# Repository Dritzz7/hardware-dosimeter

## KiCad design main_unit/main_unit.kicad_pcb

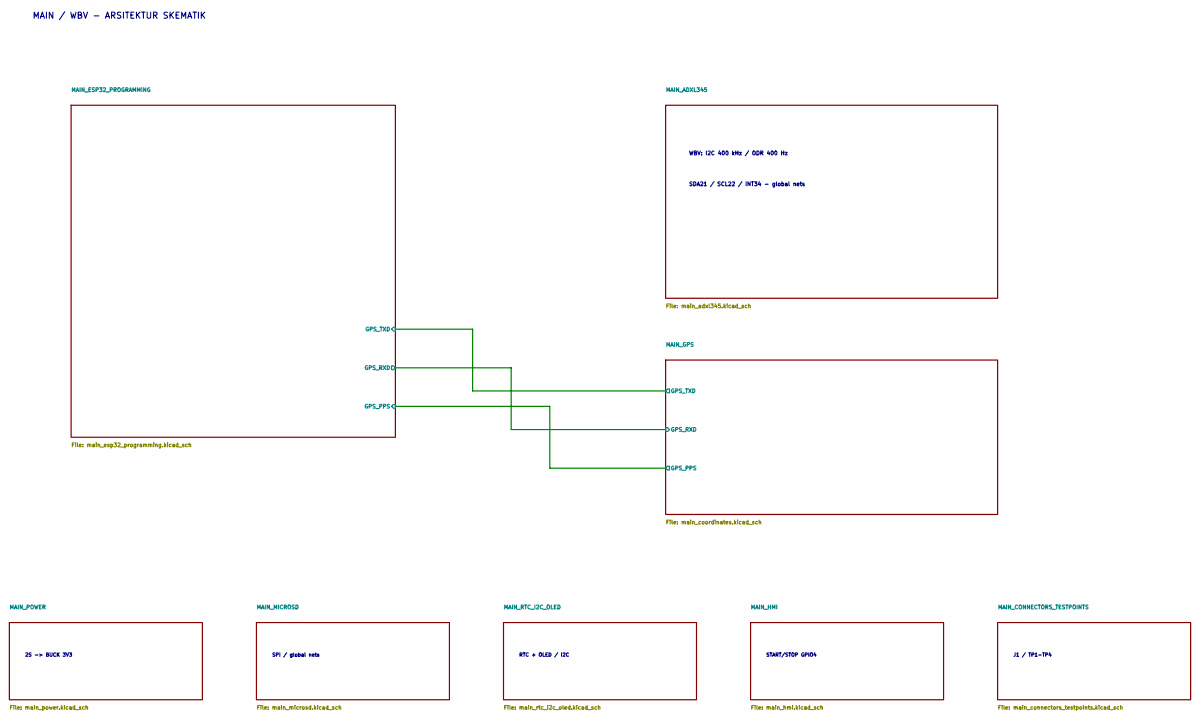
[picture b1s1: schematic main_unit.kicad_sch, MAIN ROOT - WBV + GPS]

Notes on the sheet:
2S -> BUCK 3V3
MAIN / WBV - ARSITEKTUR SKEMATIK
SPI / global nets
RTC + OLED / I2C
WBV: I2C 400 kHz / ODR 400 Hz
START/STOP GPIO4
SDA21 / SCL22 / INT34 - global nets
J1 / TP1-TP4

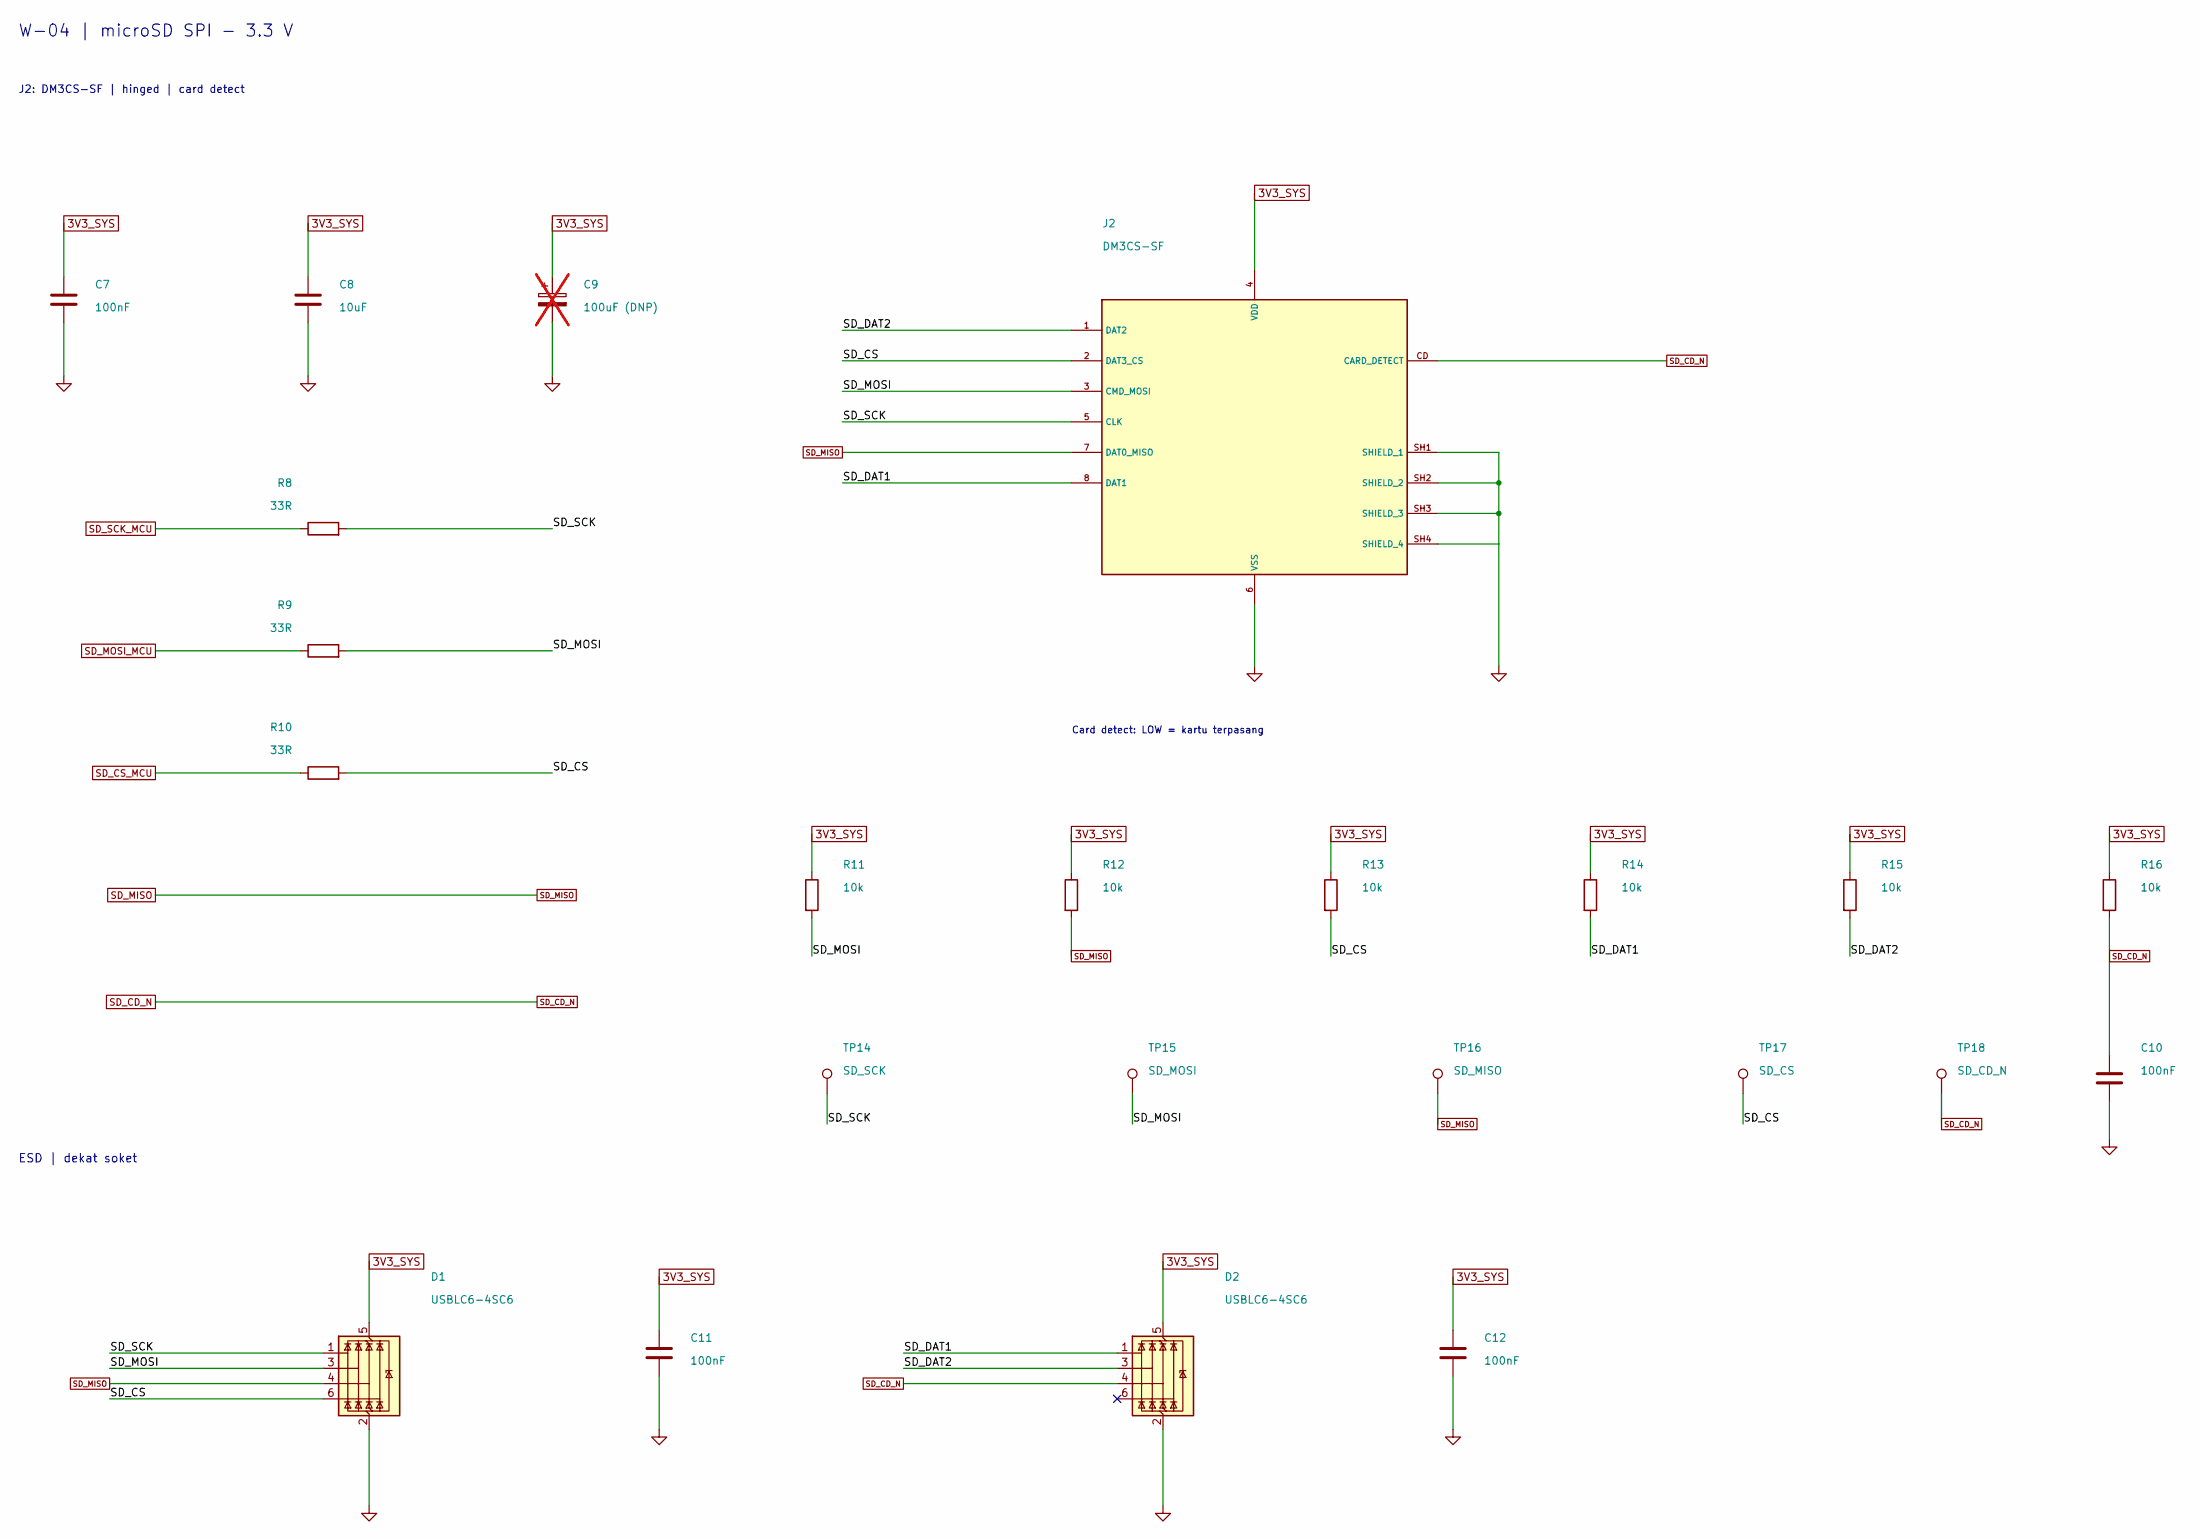
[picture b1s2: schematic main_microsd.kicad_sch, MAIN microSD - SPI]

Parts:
C7, C10, C11, C12: 100nF; C_0805_2012Metric; MPN C0805C104K5RACTU; LCSC Part # C3018562
C8: 10uF; C_0805_2012Metric; MPN CL21A106KAYNNNE; LCSC Part # C15850
C9: 100uF (DNP); CP_Radial_D5.0mm_P2.00mm_H11mm_Panasonic_FR; MPN EEUFR1C101; not fitted
D1, D2: USBLC6-4SC6; SOT-23-6_USBLC6-4SC6_ST; MPN USBLC6-4SC6; LCSC Part # C111212
J2: DM3CS-SF; microSD_Hirose_DM3CS-SF; MPN DM3CS-SF; LCSC Part # C202111
R8, R9, R10: 33R; R_0805_2012Metric; MPN RC0805FR-0733RL; LCSC Part # C126353
R11, R12, R13, R14, R15, R16: 10k; R_0805_2012Metric; MPN RC0805FR-0710KL; LCSC Part # C84376
TP14: SD_SCK; TestPoint_Pad_D1.5mm; MPN N/A - PCB copper feature
TP15: SD_MOSI; TestPoint_Pad_D1.5mm; MPN N/A - PCB copper feature
TP16: SD_MISO; TestPoint_Pad_D1.5mm; MPN N/A - PCB copper feature
TP17: SD_CS; TestPoint_Pad_D1.5mm; MPN N/A - PCB copper feature
TP18: SD_CD_N; TestPoint_Pad_D1.5mm; MPN N/A - PCB copper feature

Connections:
3V3_SYS: C7.1, C8.1, C9.1, C11.1, C12.1, D1.5 (VBUS), D2.5 (VBUS), J2.4 (VDD), R11.1, R12.1, R13.1, R14.1, R15.1, R16.1; also elsewhere on the board
/MAIN_MICROSD/SD_CS: D1.6 (I/O4), J2.2 (DAT3_CS), R10.2, R13.2, TP17.1 (1_1)
/MAIN_MICROSD/SD_DAT1: D2.1 (I/O1), J2.8 (DAT1), R14.2
/MAIN_MICROSD/SD_DAT2: D2.3 (I/O2), J2.1 (DAT2), R15.2
/MAIN_MICROSD/SD_MOSI: D1.3 (I/O2), J2.3 (CMD_MOSI), R9.2, R11.2, TP15.1 (1_1)
/MAIN_MICROSD/SD_SCK: D1.1 (I/O1), J2.5 (CLK), R8.2, TP14.1 (1_1)
GND: C7.2, C8.2, C9.2, C10.2, C11.2, C12.2, D1.2 (GND), D2.2 (GND), J2.6 (VSS), J2.SH1 (SHIELD_1), J2.SH2 (SHIELD_2), J2.SH3 (SHIELD_3), J2.SH4 (SHIELD_4); also elsewhere on the board
SD_CD_N: C10.1, D2.4 (I/O3), J2.CD (CARD_DETECT), R16.2, TP18.1 (1_1); also elsewhere on the board
SD_CS_MCU: R10.1; also elsewhere on the board
SD_MISO: D1.4 (I/O3), J2.7 (DAT0_MISO), R12.2, TP16.1 (1_1); also elsewhere on the board
SD_MOSI_MCU: R9.1; also elsewhere on the board
SD_SCK_MCU: R8.1; also elsewhere on the board

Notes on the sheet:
Card detect: LOW = kartu terpasang
ESD | dekat soket
W-04 | microSD SPI - 3.3 V
J2: DM3CS-SF | hinged | card detect

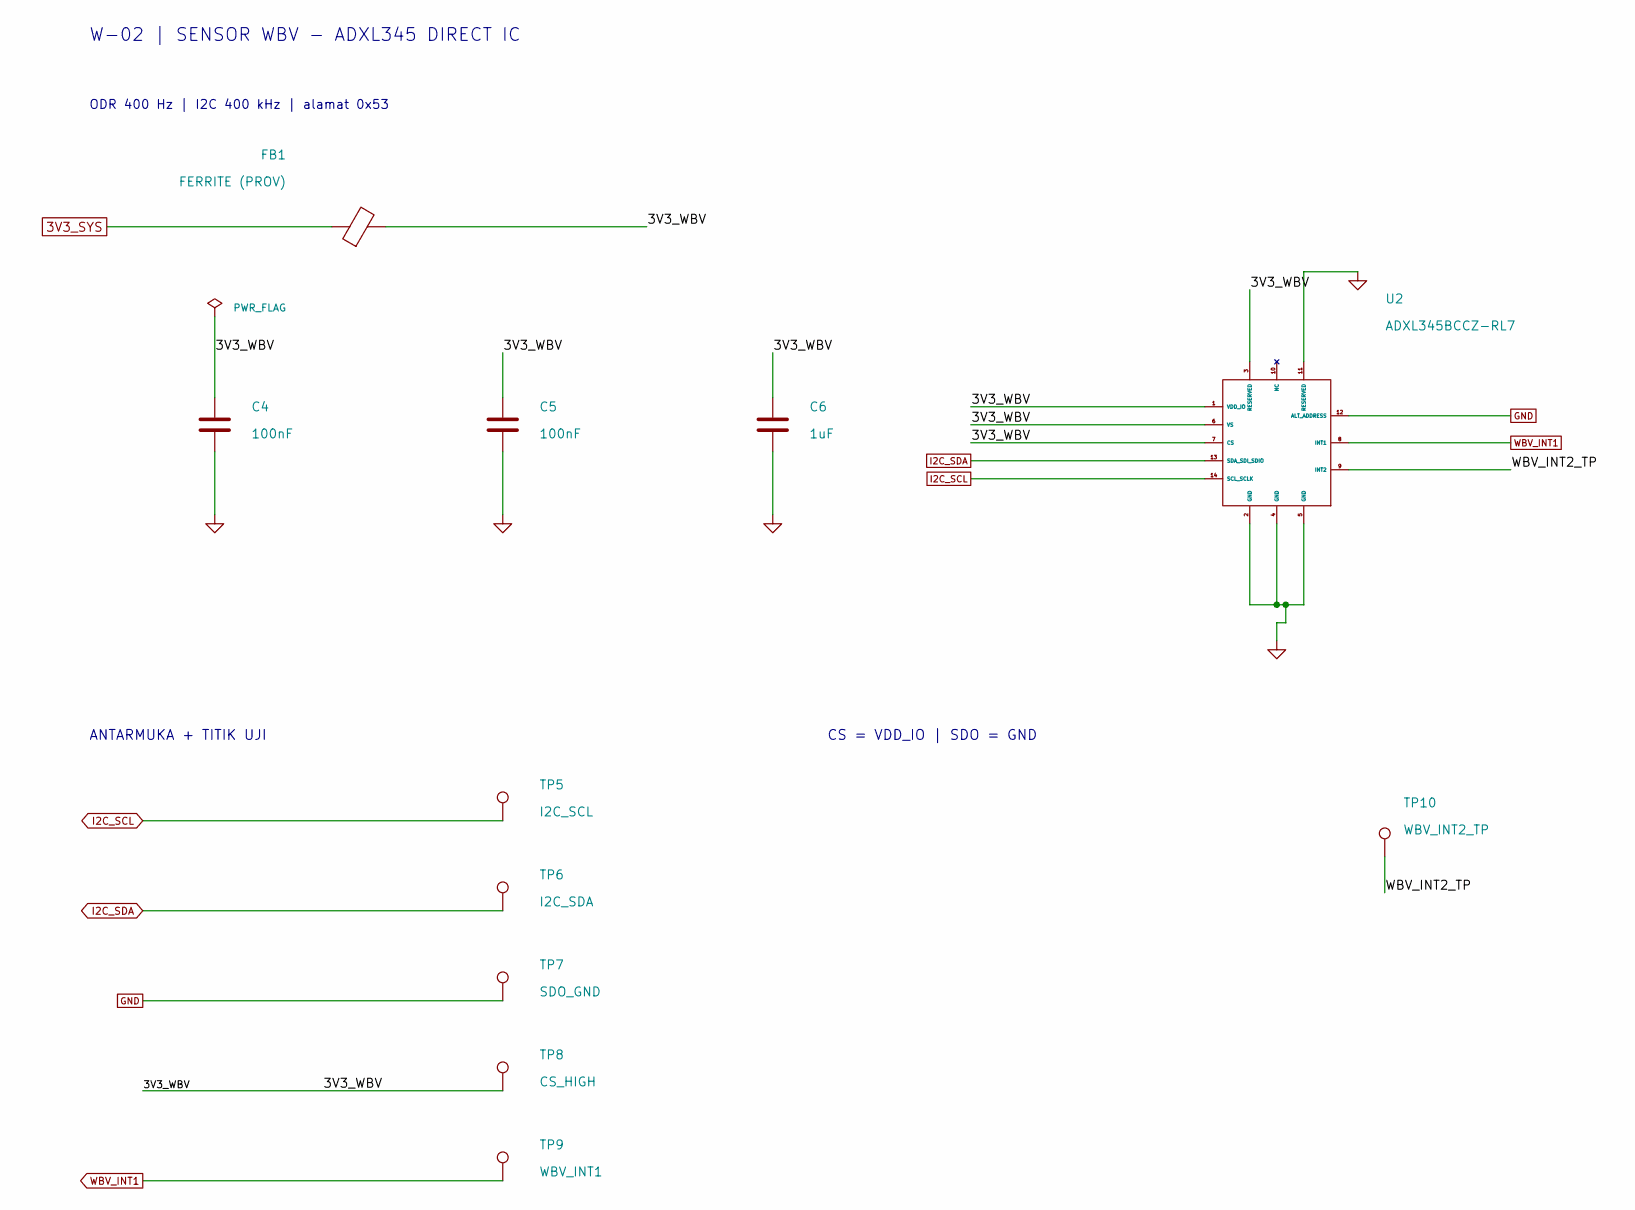
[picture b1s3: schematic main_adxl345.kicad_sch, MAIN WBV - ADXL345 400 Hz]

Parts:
C4, C5: 100nF; C_0805_2012Metric; MPN C0805C104K5RACTU; LCSC Part # C3018562
C6: 1uF; C_0805_2012Metric; MPN C0805C105K4RACTU; LCSC Part # C2167376
FB1: FERRITE (PROV); L_0805_2012Metric; MPN BLM21PG601SN1D; LCSC Part # C41556732
TP5: I2C_SCL; TestPoint_Pad_D1.5mm; MPN N/A - PCB copper feature
TP6: I2C_SDA; TestPoint_Pad_D1.5mm; MPN N/A - PCB copper feature
TP7: SDO_GND; TestPoint_Pad_D1.5mm; MPN N/A - PCB copper feature
TP8: CS_HIGH; TestPoint_Pad_D1.5mm; MPN N/A - PCB copper feature
TP9: WBV_INT1; TestPoint_Pad_D1.5mm; MPN N/A - PCB copper feature
TP10: WBV_INT2_TP; TestPoint_Pad_D1.5mm; MPN N/A - PCB copper feature
U2: ADXL345BCCZ-RL7; ADXL345_CC-14-1_ADI_JLC; MPN ADXL345BCCZ-RL7; LCSC Part # C9667

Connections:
3V3_SYS: FB1.1; also elsewhere on the board
/MAIN_ADXL345/3V3_WBV: C4.1, C5.1, C6.1, FB1.2, TP8.1 (1_1), U2.1 (VDD_IO), U2.3 (RESERVED), U2.6 (VS), U2.7 (CS)
/MAIN_ADXL345/WBV_INT2_TP: TP10.1 (1_1), U2.9 (INT2)
GND: C4.2, C5.2, C6.2, TP7.1 (1_1), U2.2 (GND), U2.4 (GND), U2.5 (GND), U2.11 (RESERVED), U2.12 (ALT_ADDRESS); also elsewhere on the board
I2C_SCL: TP5.1 (1_1), U2.14 (SCL_SCLK); also elsewhere on the board
I2C_SDA: TP6.1 (1_1), U2.13 (SDA_SDI_SDIO); also elsewhere on the board
WBV_INT1: TP9.1 (1_1), U2.8 (INT1); also elsewhere on the board

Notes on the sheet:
W-02 | SENSOR WBV - ADXL345 DIRECT IC
ODR 400 Hz | I2C 400 kHz | alamat 0x53
ANTARMUKA + TITIK UJI
CS = VDD_IO | SDO = GND

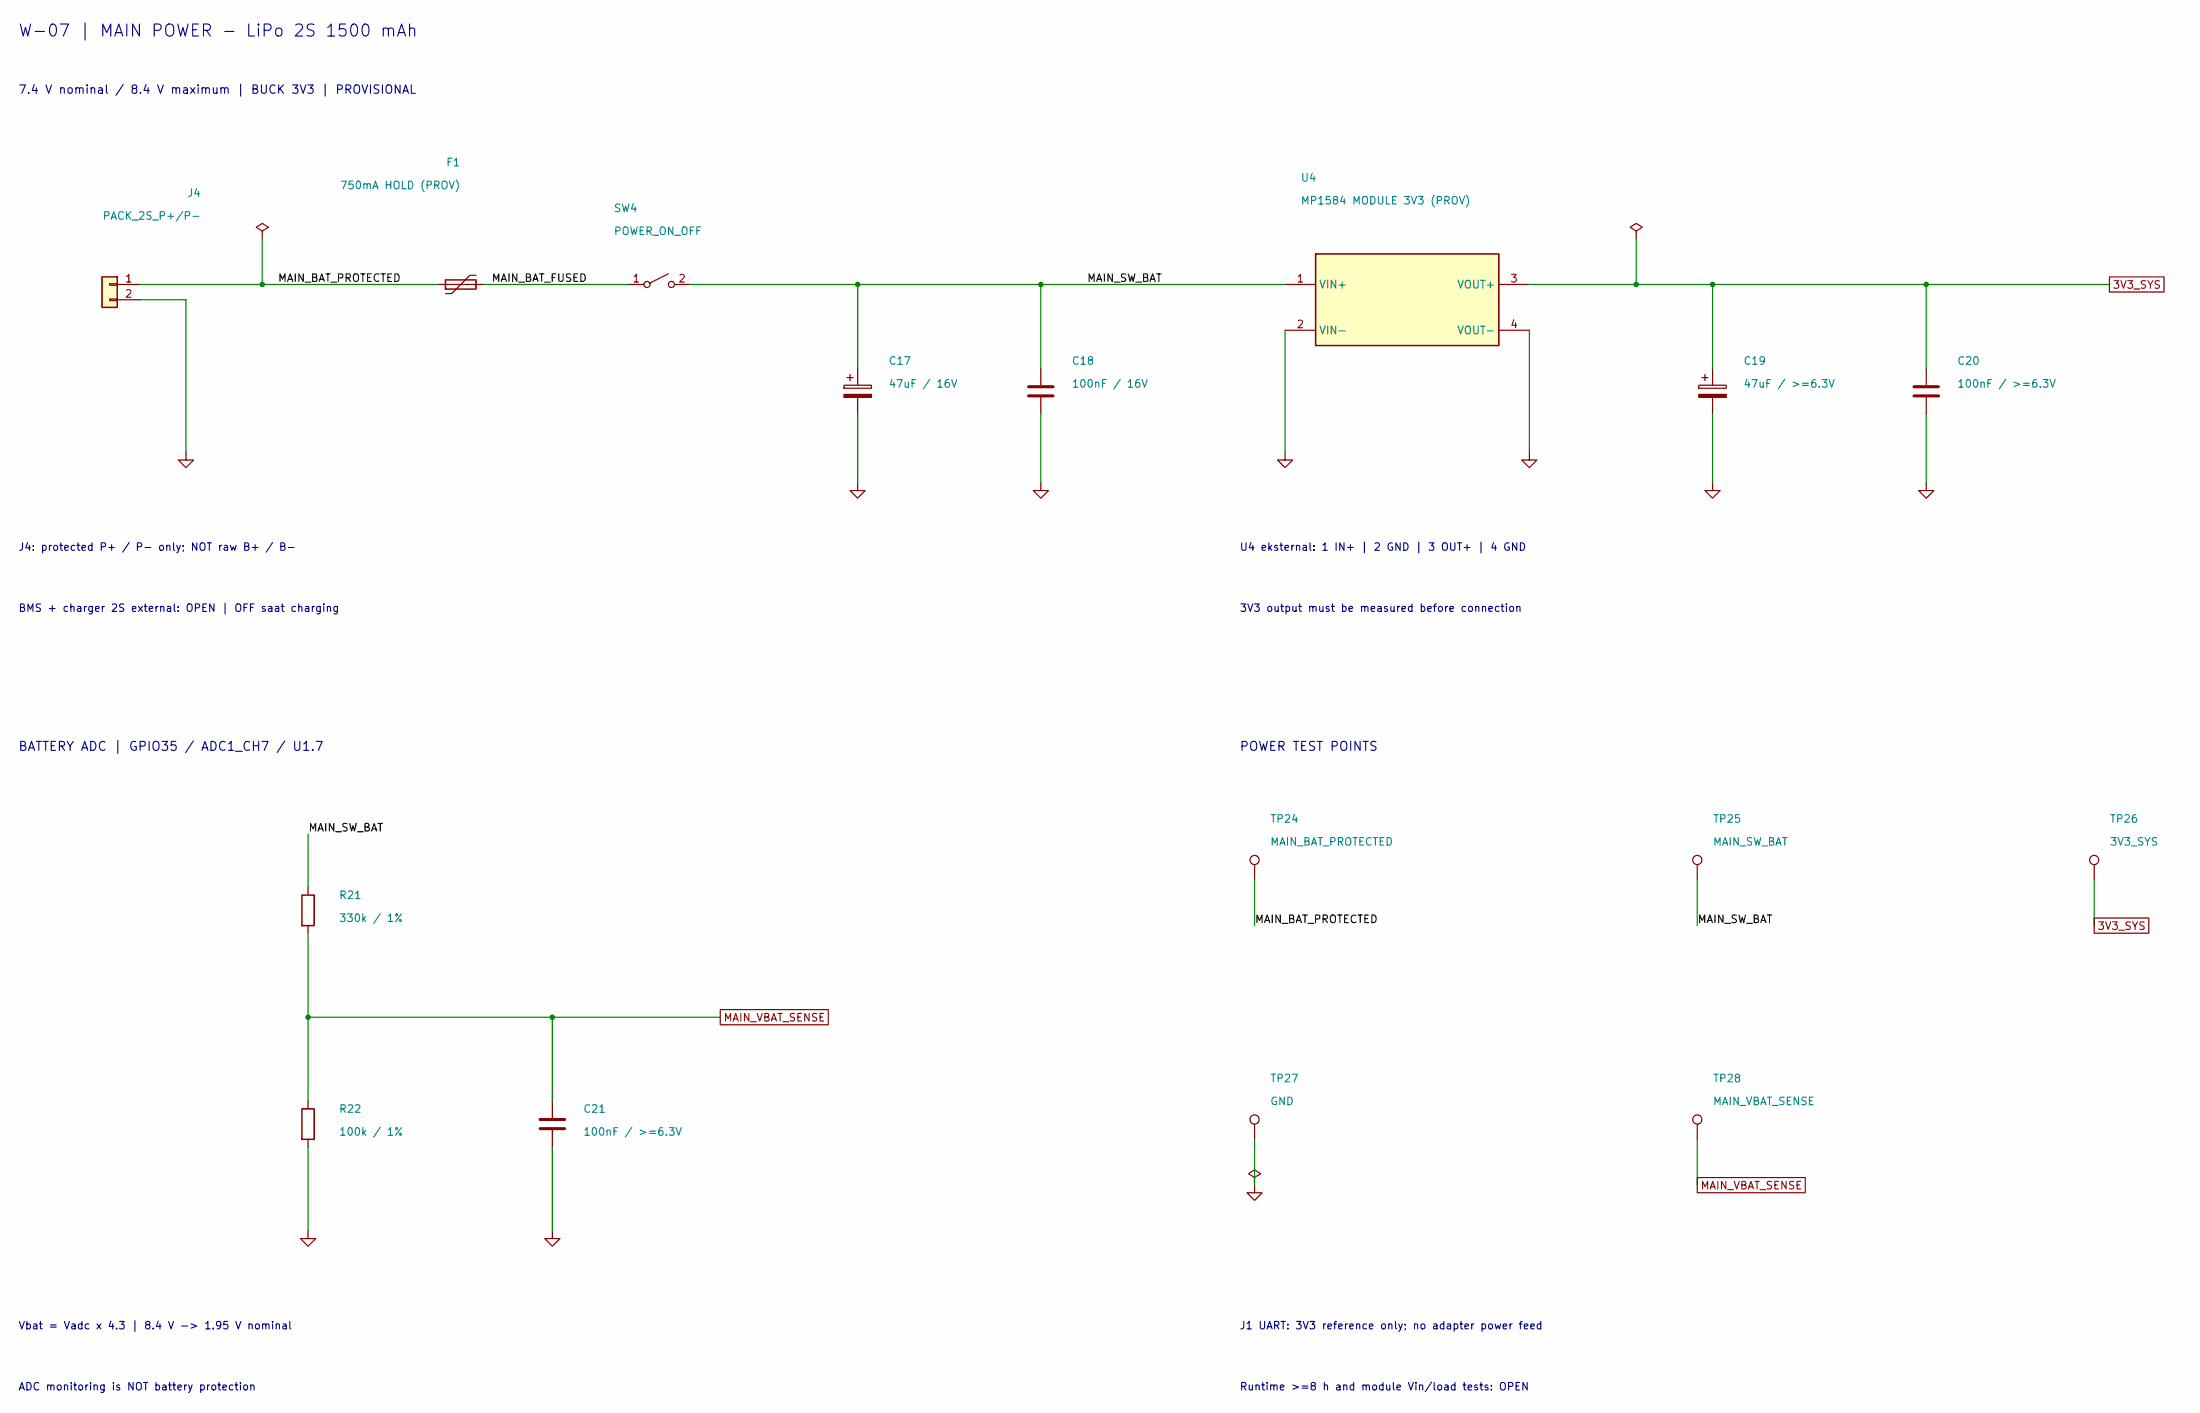
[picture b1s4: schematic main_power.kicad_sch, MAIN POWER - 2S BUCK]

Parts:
C17: 47uF / 16V; CP_Radial_D5.0mm_P2.00mm_H11mm_Panasonic_FR; MPN EEUFR1E470; LCSC Part # C407893
C18: 100nF / 16V; C_0805_2012Metric; MPN C0805C104K5RACTU; LCSC Part # C3018562
C19: 47uF / >=6.3V; CP_Radial_D5.0mm_P2.00mm_H11mm_Panasonic_FR; MPN EEUFR1E470; LCSC Part # C407893
C20, C21: 100nF / >=6.3V; C_0805_2012Metric; MPN C0805C104K5RACTU; LCSC Part # C3018562
F1: 750mA HOLD (PROV); Fuse_Bourns_MF-MSMF075_1812_Style1; MPN MF-MSMF075-2; LCSC Part # C84140
J4: PACK_2S_P+/P-; JST_XH_B2B-XH-A_1x02_P2.50mm_Vertical; MPN B2B-XH-A(LF)(SN); LCSC Part # C158012
R21: 330k / 1%; R_0805_2012Metric; MPN RC0805FR-07330KL; LCSC Part # C114528
R22: 100k / 1%; R_0805_2012Metric; MPN RC0805FR-07100KL; LCSC Part # C96346
SW4: POWER_ON_OFF; SolderWire-0.25sqmm_1x02_P4.2mm_D0.65mm_OD1.7mm; MPN OPEN - verify purchased part
TP24: MAIN_BAT_PROTECTED; TestPoint_Pad_D1.5mm; MPN N/A - PCB copper feature
TP25: MAIN_SW_BAT; TestPoint_Pad_D1.5mm; MPN N/A - PCB copper feature
TP26: 3V3_SYS; TestPoint_Pad_D1.5mm; MPN N/A - PCB copper feature
TP27: GND; TestPoint_Pad_D1.5mm; MPN N/A - PCB copper feature
TP28: MAIN_VBAT_SENSE; TestPoint_Pad_D1.5mm; MPN N/A - PCB copper feature
U4: MP1584 MODULE 3V3 (PROV); SolderWire-0.25sqmm_1x04_P4.2mm_D0.65mm_OD1.7mm; MPN OPEN - verify purchased part

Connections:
3V3_SYS: C19.1, C20.1, TP26.1 (1_1), U4.3 (VOUT+); also elsewhere on the board
/MAIN_POWER/MAIN_BAT_FUSED: F1.2, SW4.1 (A)
/MAIN_POWER/MAIN_BAT_PROTECTED: F1.1, J4.1, TP24.1 (1_1)
/MAIN_POWER/MAIN_SW_BAT: C17.1, C18.1, R21.1, SW4.2 (B), TP25.1 (1_1), U4.1 (VIN+)
GND: C17.2, C18.2, C19.2, C20.2, C21.2, J4.2, R22.2, TP27.1 (1_1), U4.2 (VIN-), U4.4 (VOUT-); also elsewhere on the board
MAIN_VBAT_SENSE: C21.1, R21.2, R22.1, TP28.1 (1_1); also elsewhere on the board

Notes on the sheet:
ADC monitoring is NOT battery protection
POWER TEST POINTS
Vbat = Vadc x 4.3 | 8.4 V -> 1.95 V nominal
Runtime >=8 h and module Vin/load tests: OPEN
J1 UART: 3V3 reference only; no adapter power feed
3V3 output must be measured before connection
U4 eksternal: 1 IN+ | 2 GND | 3 OUT+ | 4 GND
J4: protected P+ / P- only; NOT raw B+ / B-
7.4 V nominal / 8.4 V maximum | BUCK 3V3 | PROVISIONAL
BMS + charger 2S external: OPEN | OFF saat charging
W-07 | MAIN POWER - LiPo 2S 1500 mAh
BATTERY ADC | GPIO35 / ADC1_CH7 / U1.7

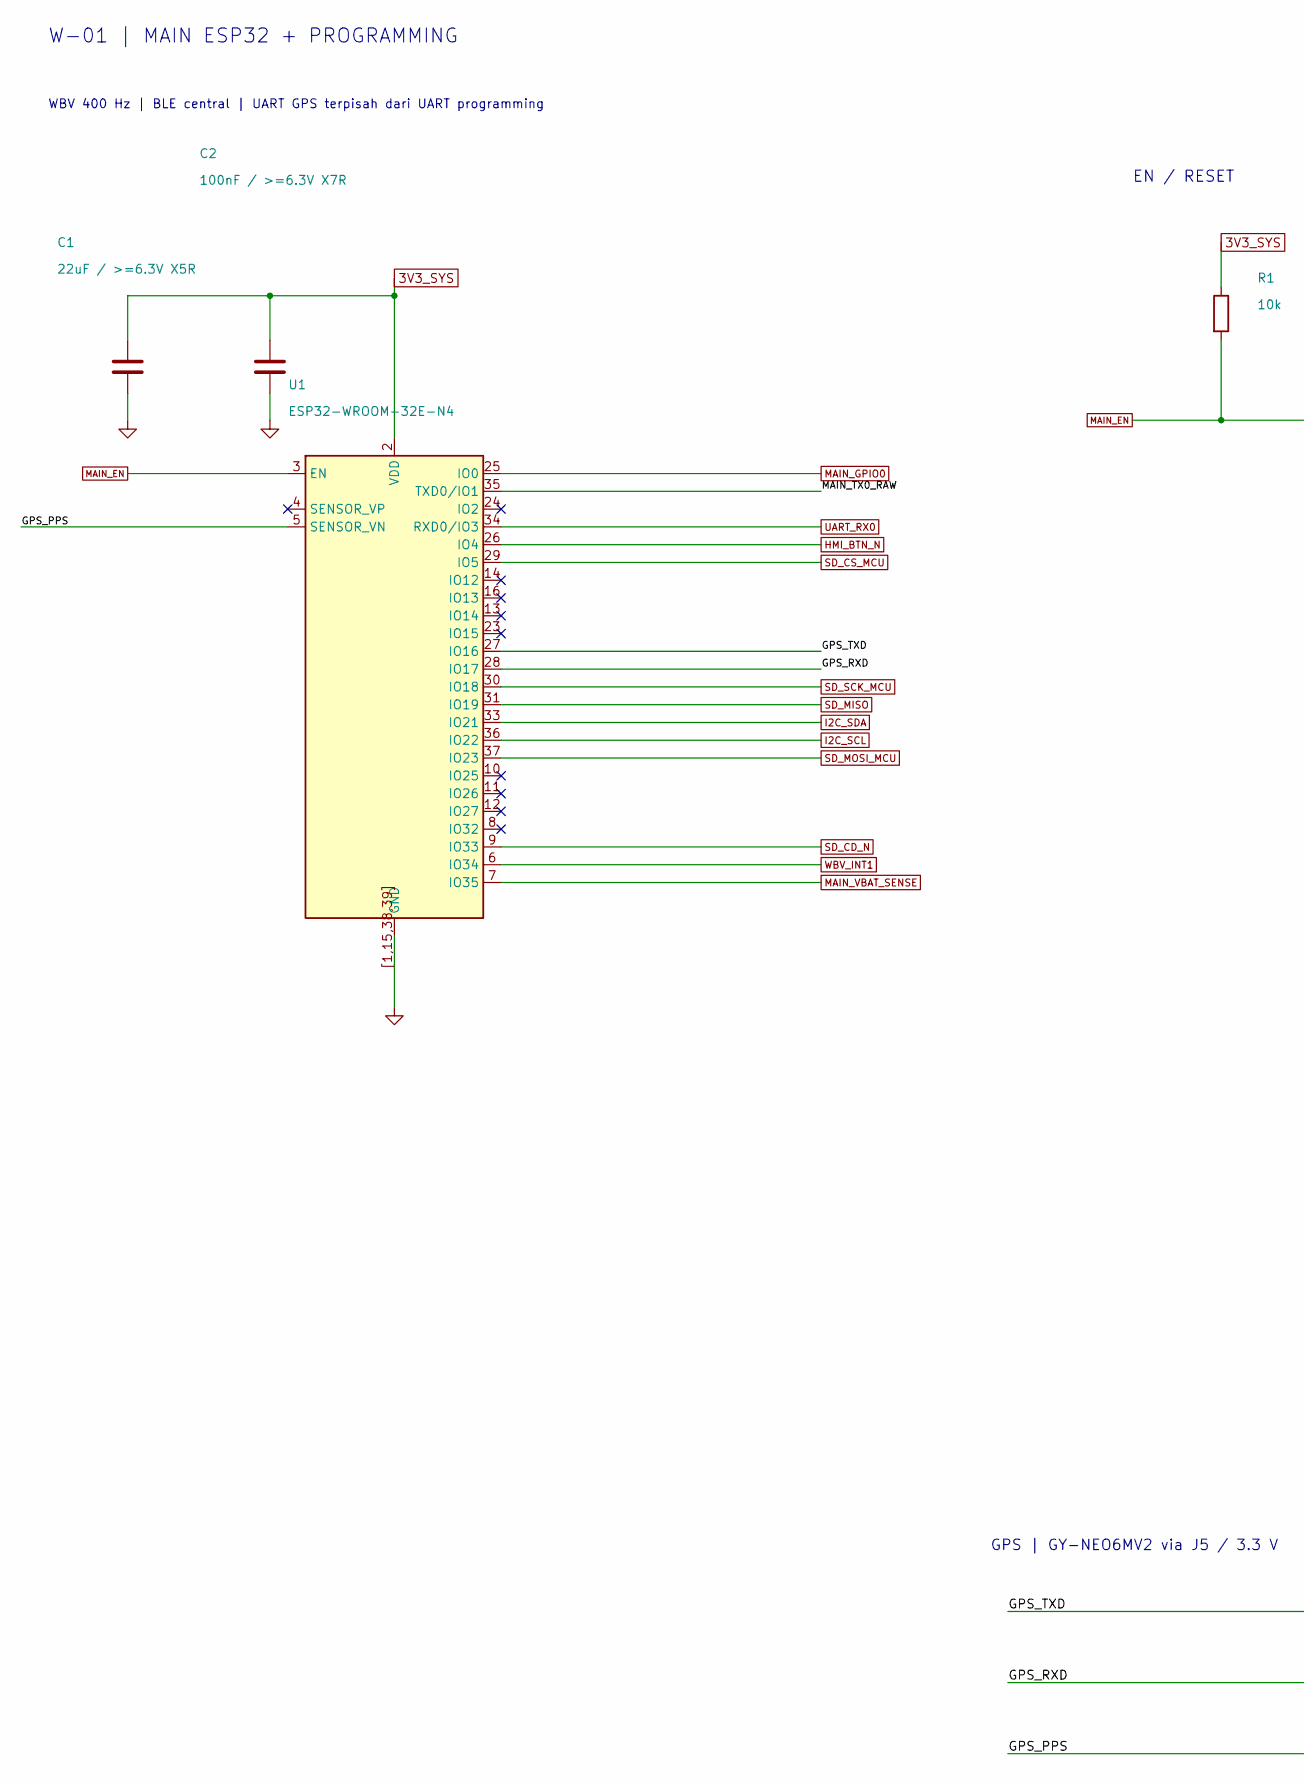
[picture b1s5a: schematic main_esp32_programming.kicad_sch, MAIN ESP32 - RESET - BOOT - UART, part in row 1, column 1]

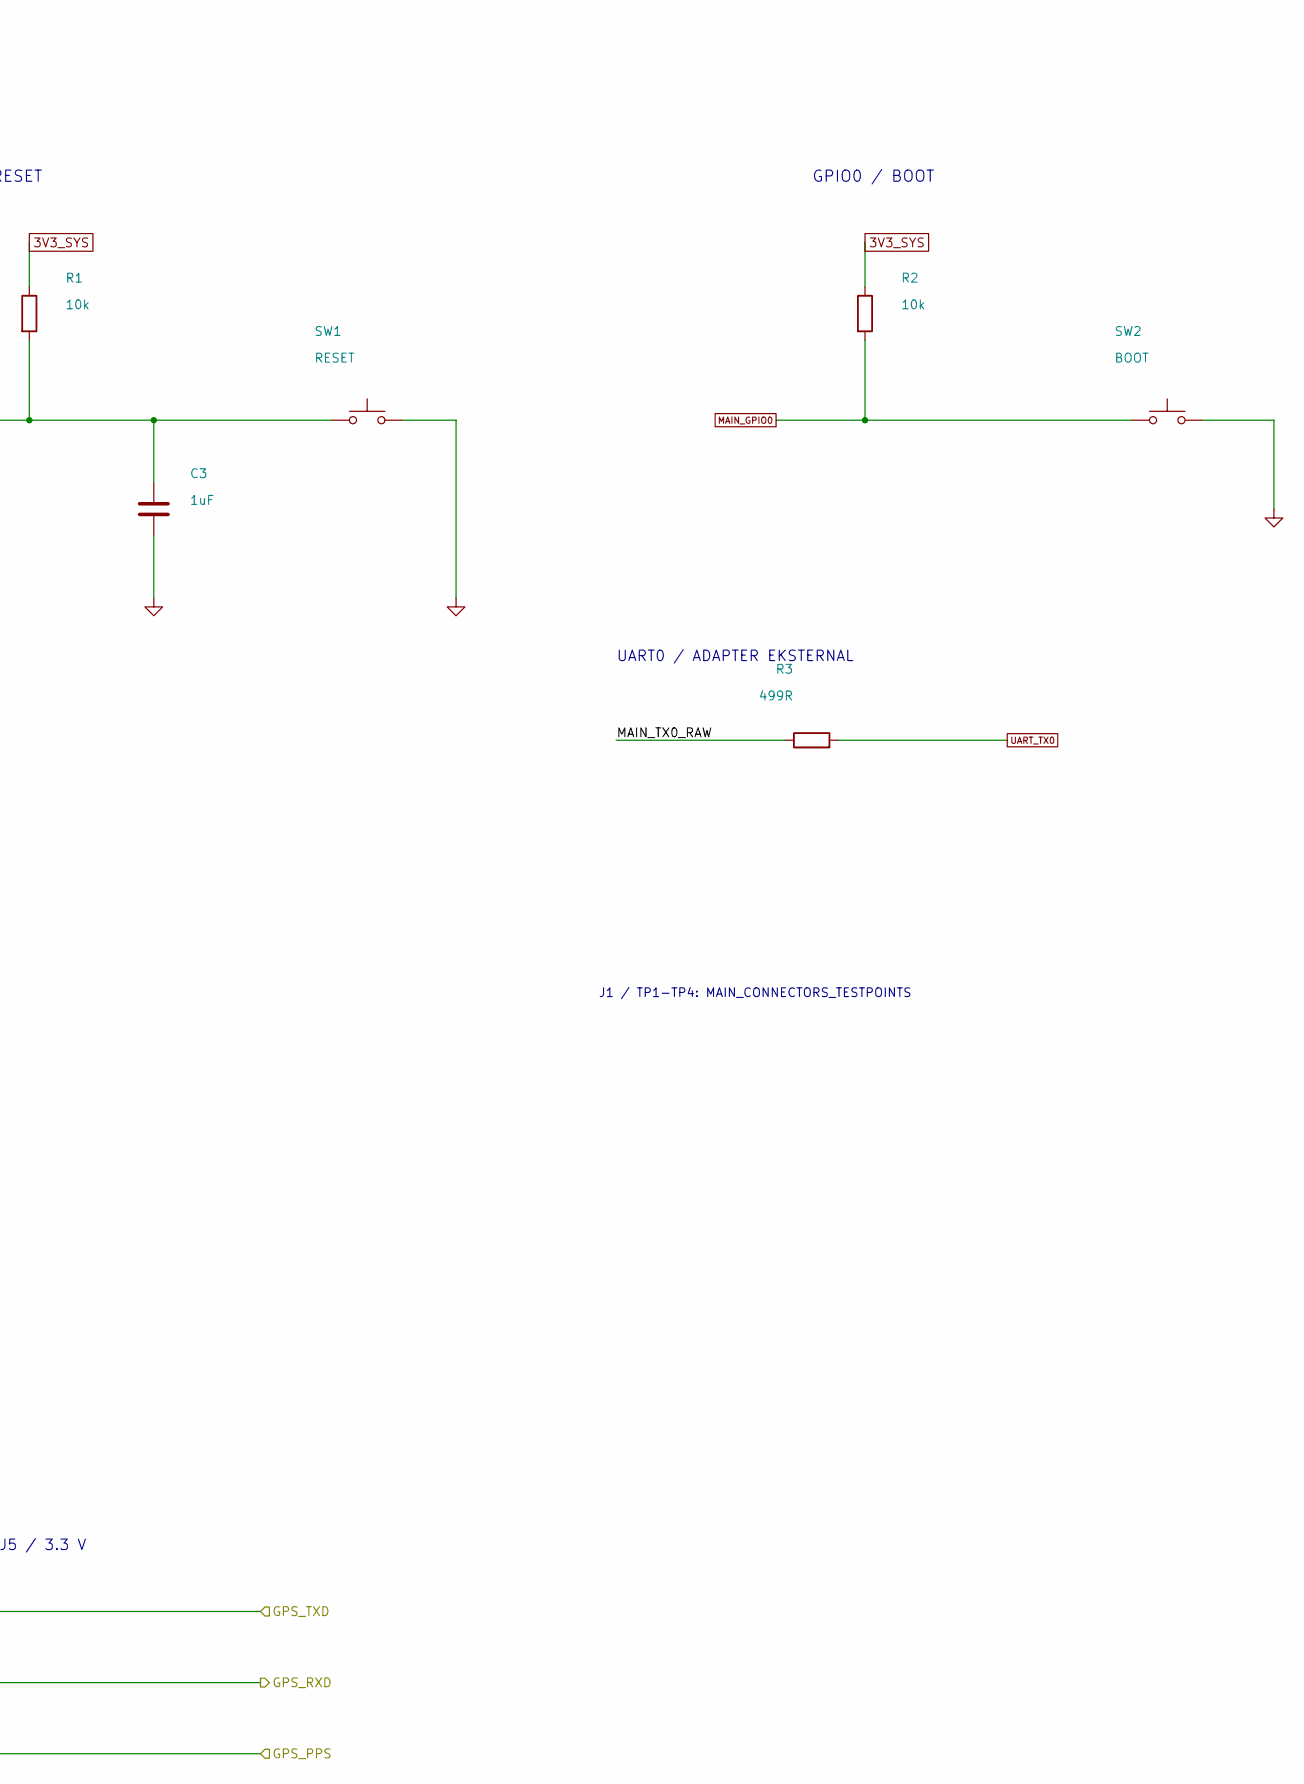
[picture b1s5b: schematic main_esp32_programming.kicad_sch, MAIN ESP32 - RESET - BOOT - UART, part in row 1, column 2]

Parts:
C1: 22uF / >=6.3V X5R; C_1206_3216Metric; MPN CL31A226KOHNNNE; LCSC Part # C90146
C2: 100nF / >=6.3V X7R; C_0805_2012Metric; MPN C0805C104K5RACTU; LCSC Part # C3018562
C3: 1uF; C_0805_2012Metric; MPN C0805C105K4RACTU; LCSC Part # C2167376
R1, R2: 10k; R_0805_2012Metric; MPN RC0805FR-0710KL; LCSC Part # C84376
R3: 499R; R_0805_2012Metric; MPN RC0805FR-07499RL; LCSC Part # C130458
SW1: RESET; SW_PUSH_6mm_H4.3mm; MPN B3F-1000; LCSC Part # C93157
SW2: BOOT; SW_PUSH_6mm_H4.3mm; MPN B3F-1000; LCSC Part # C93157
U1: ESP32-WROOM-32E-N4; ESP32-WROOM-32E_JLC_NoVia; MPN ESP32-WROOM-32E-N4; LCSC Part # C701341

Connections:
3V3_SYS: C1.1, C2.1, R1.1, R2.1, U1.2 (VDD); also elsewhere on the board
/MAIN_ESP32_PROGRAMMING/GPS_PPS: U1.5 (SENSOR_VN); also elsewhere on the board
/MAIN_ESP32_PROGRAMMING/GPS_RXD: U1.28 (IO17); also elsewhere on the board
/MAIN_ESP32_PROGRAMMING/GPS_TXD: U1.27 (IO16); also elsewhere on the board
/MAIN_ESP32_PROGRAMMING/MAIN_TX0_RAW: R3.1, U1.35 (TXD0/IO1)
GND: C1.2, C2.2, C3.2, SW1.2, SW2.2, U1.1 (GND), U1.15 (GND), U1.38 (GND), U1.39 (GND), U1.[1,15,38,39] (GND); also elsewhere on the board
HMI_BTN_N: U1.26 (IO4); also elsewhere on the board
I2C_SCL: U1.36 (IO22); also elsewhere on the board
I2C_SDA: U1.33 (IO21); also elsewhere on the board
MAIN_EN: C3.1, R1.2, SW1.1, U1.3 (EN); also elsewhere on the board
MAIN_GPIO0: R2.2, SW2.1, U1.25 (IO0); also elsewhere on the board
MAIN_VBAT_SENSE: U1.7 (IO35); also elsewhere on the board
SD_CD_N: U1.9 (IO33); also elsewhere on the board
SD_CS_MCU: U1.29 (IO5); also elsewhere on the board
SD_MISO: U1.31 (IO19); also elsewhere on the board
SD_MOSI_MCU: U1.37 (IO23); also elsewhere on the board
SD_SCK_MCU: U1.30 (IO18); also elsewhere on the board
UART_RX0: U1.34 (RXD0/IO3); also elsewhere on the board
UART_TX0: R3.2; also elsewhere on the board
WBV_INT1: U1.6 (IO34); also elsewhere on the board

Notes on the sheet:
W-01 | MAIN ESP32 + PROGRAMMING
GPS | GY-NEO6MV2 via J5 / 3.3 V
UART0 / ADAPTER EKSTERNAL
WBV 400 Hz | BLE central | UART GPS terpisah dari UART programming
GPIO0 / BOOT
EN / RESET
J1 / TP1-TP4: MAIN_CONNECTORS_TESTPOINTS

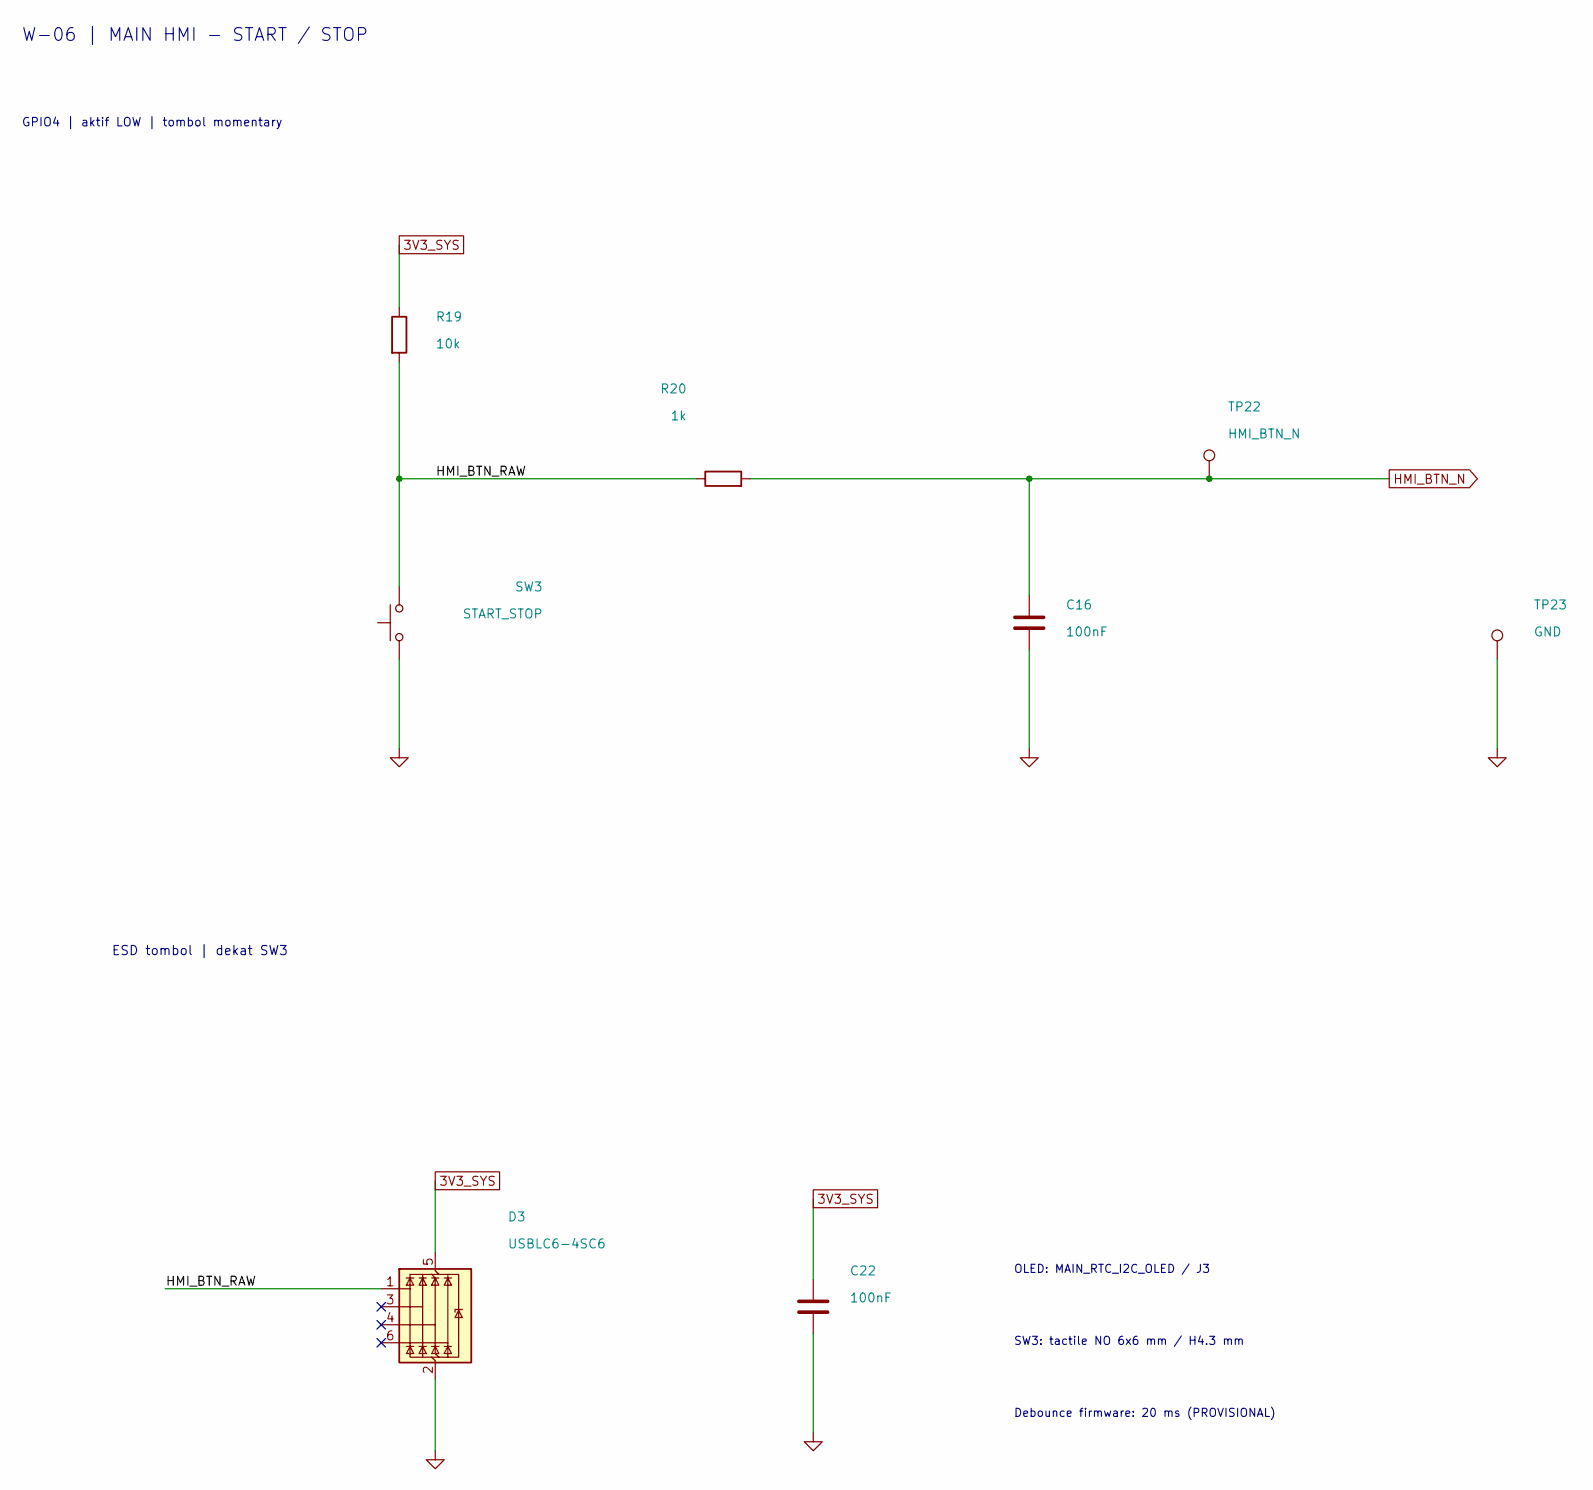
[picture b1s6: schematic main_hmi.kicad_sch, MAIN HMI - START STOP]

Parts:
C16, C22: 100nF; C_0805_2012Metric; MPN C0805C104K5RACTU; LCSC Part # C3018562
D3: USBLC6-4SC6; SOT-23-6_USBLC6-4SC6_ST; MPN USBLC6-4SC6; LCSC Part # C111212
R19: 10k; R_0805_2012Metric; MPN RC0805FR-0710KL; LCSC Part # C84376
R20: 1k; R_0805_2012Metric; MPN RC0805FR-071KL; LCSC Part # C95781
SW3: START_STOP; SW_PUSH_6mm_H4.3mm; MPN B3F-1000; LCSC Part # C93157
TP22: HMI_BTN_N; TestPoint_Pad_D1.5mm; MPN N/A - PCB copper feature
TP23: GND; TestPoint_Pad_D1.5mm; MPN N/A - PCB copper feature

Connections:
3V3_SYS: C22.1, D3.5 (VBUS), R19.1; also elsewhere on the board
/MAIN_HMI/HMI_BTN_RAW: D3.1 (I/O1), R19.2, R20.1, SW3.2
GND: C16.2, C22.2, D3.2 (GND), SW3.1, TP23.1 (1_1); also elsewhere on the board
HMI_BTN_N: C16.1, R20.2, TP22.1 (1_1); also elsewhere on the board

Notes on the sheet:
W-06 | MAIN HMI - START / STOP
SW3: tactile NO 6x6 mm / H4.3 mm
ESD tombol | dekat SW3
OLED: MAIN_RTC_I2C_OLED / J3
Debounce firmware: 20 ms (PROVISIONAL)
GPIO4 | aktif LOW | tombol momentary
